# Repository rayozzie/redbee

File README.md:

#RedBee project

##About the RedBee project
RedBee was developed in support of [Safecast](http://blog.safecast.org/), a global volunter-centered citizen science project working to empower people with data about their environments. More specifically, it is made for integrating with Safecast's [bGeigie Nano](http://blog.safecast.org/bgeigie-nano/). 

##What does the RedBee do?
The RedBee allows for simple adaptation of the [RedBear BLE Nano](http://redbearlab.com/blenano/) to the bGeigie Nano XBee socket for integrating Bluetooth Low Energy functionality. The ReadBear BLE Nano uses Raytac's MDBT40 Bluetooth 4.0 radio module. Read more about Raytac's MDBT40 [here](https://www.nordicsemi.com/eng/Products/Bluetooth-Smart-Bluetooth-low-energy/nRF51822).

##What else can the RedBee be used for?
The RedBee also makes it easy to connect the [RedBear BLE Nano](http://redbearlab.com/blenano/) to any standard XBee socket where a standard UART communication interface is needed. The UART communication interface signals are (DTE perspective):
* TX: Transmit. The TX pin on the RedBee is an output (driver).
* RX: Receive. The RX pin on the RedBee is an input (high impedance).
* CTS: Clear-To-Send. The CTS pin on the RedBee is an output (driver).
* RTS: Request-To-Send. The RTS pin on the RedBee is an input (high impedance).

Custom firmware can be developed for the RedBear BLE Nano using the mbed's online IDE (Integraged Development Environment); however, the RedBear BLE Nano cannot be programmed directly from the RedBee PCB with the mbed IDE. Instead you must use RedBear Lab's USB adapter for programming. Alternatively, since the Raytac MDBT40 supports wireless DFU (device firmware update) over bluetooth, and therefore the ReadBear BLE Nano, this feature can be used for updating firmware wirelessly while in the RedBee configuration.

##How do I get a RedBee PCB?
There are a few options for getting the RedBee PCB:
* Use latest version of gerber files (PCB fabrication files) archived in this respository under RedBee/Hardware/Gerbers/Archive. 

   Note: these files can be sent to any PCB fabricator to build. You will have to specify the soldermask color, red. Some PCB fabricators only offer certain soldermask colors. Most commonly, unspecified soldermask color will be green. OSH Park, for example, uses only their signature color, purple.
* Buy from [Casco Logix](http://www.cascologix.com/store/p33/RedBee.html) on the Casco Logix store page.
* Buy from Casco Logix on [Tindie](https://www.tindie.com/stores/CascoLogix/).

##What headers should I use for the RedBee?
1. XBee Header [Harwin M22-2511005](http://www.digikey.com/product-detail/en/harwin-inc/M22-2511005/952-1316-ND/2264297)
2. RedBear BLE Nano Header [Sullins PPTC061LFBN-RC](http://www.digikey.com/product-detail/en/sullins-connector-solutions/PPTC061LFBN-RC/S7004-ND/810145)

   Note: this header is optional. The ReadBear BLE Nano can be mounted directly to the RedBee PCB for more permanent and lower-profile needs.

##Working with the RedBee native design files
RedBee was designed using [KiCAD](http://kicad.org/). KiCAD is an open source EDA (Electronic Design Automation) software package that supports multiple schematic pages, unlimited PCB outline, up to 32 PCB layers and gerber file output for free! 

All of the native KiCAD design files can be found in this repository under RedBee/Hardware/EDA. The schematic and PCB library files for both the XBee 2mm male pin headers and the RedBear BLE Nano 100mil female headers will not be found in the KiCAD default libraries included with the KiCAD install. Instead, the PCB footprints can be found in this repository under RedBee/Hardware/EDA/Footprint_Archive.pretty. The schematic should open and display the original schematic component decals without any manual intervention, as these decals are archived in the *-cache.lib file in the EDA directory. Once the schematic is opened, these decals can be saved to your own schematic library if desired.

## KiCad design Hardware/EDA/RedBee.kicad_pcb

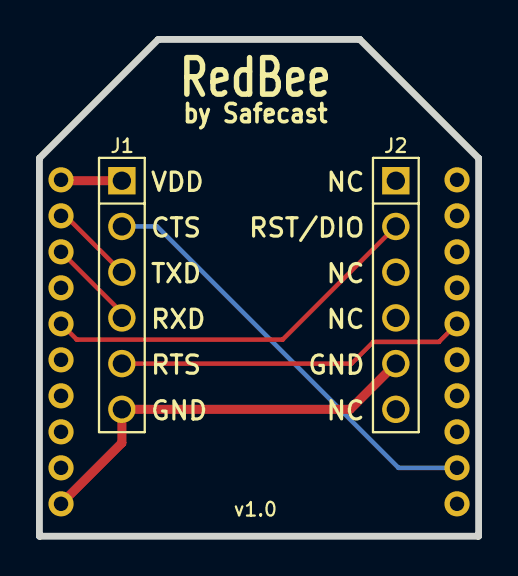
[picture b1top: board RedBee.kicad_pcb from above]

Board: 2 copper layers, 24.4 x 27.6 mm, 3 parts (1 on the bottom side), 7 nets.

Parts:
J1, J2: HEADER_F_2.54MM_1R6P_ST_AU_PTH
P1: HEADER_M_XBEE_PTH; HEADER_XBEE

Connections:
CTS_HEADER: J1.2, P1.12
GND: J1.6, J2.5, P1.10
RESET: J2.2, P1.5
RTS_HEADER: J1.5, P1.16
RXD_HEADER: J1.4, P1.3
TXD_HEADER: J1.3, P1.2
VDD: J1.1, P1.1

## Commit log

2021-11-07 Update README.md
    https://forum.kicad.info/t/warning-avoid-all-links-to-kicad-pcb-org-use-kicad-org/31521/
